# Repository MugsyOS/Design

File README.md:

# Design
All the parts! CAD, PCB and STL files for all of Mugsy's physical components. 

# Mech Control PCB
### Files:
* ****Schematic:**** mech-control-SCH-v0.2.fsch
* ****Board:**** mech-control-BRD-v0.2.fbrd
- - -

# Cone Mech
### Files:
* **Cone Pulley (2 files):** Print main and top.
* **Cone Support (1 file):** Print two for both left and right supports.
* **Stepper Motor Mount (1 file)**: Print one
* **Panels:** 
  * STLs provided for both top and bottom panels.
  * DXF files provided for those with access to a laser or CNC. We use 3mm cast acrylic which works out great. Other material can be used but must be 3mm. 
* **Idler Mount (1 File):** Print two.
- - -
### Additional Parts:
* **Stepper Motor**
  * Model:14HR05-0504S
  * Step Angle: 0.9deg
  * Single Unit Source: [STEPPERONLINE](https://www.omc-stepperonline.com/round-nema-14-bipolar-0-9deg-7ncm-9-91oz-in-0-5a-8-5v-36x12mm-4-wires-14hr05-0504s)
* **Signal** **Breakout PCB**: PCB files will be uploaded shortly. Single PCBs will also be available on the web store end of March 2024. 
* **Ethernet Socket:** RJ45 Connector, PCB Mount
* **M3 Threaded Inserts:**
  * Size: M3*4.6x5.7mm
* **M3 x 8mm Hex Head Machine Screws**
* **2GT Timing Pulley:** 
  * Type: 2M-AF
  * 20 Teeth
  * 6mm bore size
* **GT2 Toothless  Idler Pulleys (2x):** 3mm bore size
- - -
# Spout Mech
### Files:
* ****Spout Pulley Assembly (2 files):**** Print main and cap.
* ****Spout Pulley Assembly (2 files):**** Print main and cap.
* ****Spout Arm(1 file)****: Print one
- - -
### Additional Parts:
* ****Stepper Motor****
  * Model: 17HS08-1004S |
  * Step Angle: 1.8 deg
  * Single Unit Source: [STEPPERONLINE](https://www.omc-stepperonline.com/nema-17-bipolar-1-8deg-16ncm-22-6oz-in-1a-3-7v-42x42x20mm-4-wires-17hs08-1004s)
* ****M8 x 50mm Threaded Rod****
* ****8mm Shaft Lock Collar:**** 
  * 8mm(ID) * 14mm (OD) * 7mm (Depth)
* ****2GT Timing Pulley:****
  * 40 Teeth 
  * 8mm Bore Size
* ****GT2 Belt:**** 
  * 156mm * 6mm
- - -
# Screen Mount/Stabilizer
### Files:
* ****Screen Support:**** Left Side (single)
* ****Screen Support:**** Right Side (double)
* ****Screen Mount Main****: Print one
- - -
****All STEP/Fusion CAD source files will be uploaded as soon as possible.****

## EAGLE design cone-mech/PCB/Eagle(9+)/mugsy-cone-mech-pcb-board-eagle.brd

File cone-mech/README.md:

# Cone Mech
## Files:
* **Cone Pulley (2 files):** Print main and top.
* **Cone Support (1 file):** Print two for both left and right supports.
* **Stepper Motor Mount (1 file)**: Print one
* **Panels:** 
  * STLs provided for both top and bottom panels.
  * DXF files provided for those with access to a laser or CNC. We use 3mm cast acrylic which works out great. Other material can be used but must be 3mm. 
* **Idler Mount (1 File):** Print two.

## Additional Parts:
* **Stepper Motor**
  * Model:14HR05-0504S
  * Step Angle: 0.9deg
  * Single Unit Source: [STEPPERONLINE](https://www.omc-stepperonline.com/round-nema-14-bipolar-0-9deg-7ncm-9-91oz-in-0-5a-8-5v-36x12mm-4-wires-14hr05-0504s)
* **Signal** **Breakout PCB**: PCB files will be uploaded shortly. Single PCBs will also be available on the web store end of March 2024. 
* **Ethernet Socket:** RJ45 Connector, PCB Mount
* **M3 Threaded Inserts:**
  * Size: M3*4.6x5.7mm
* **M3 x 8mm Hex Head Machine Screws**
* **GT2 Timing Pulley:** 
  * Type: 2M-AF
  * 20 Teeth
  * 6mm bore size
* **GT2 Toothless  Idler Pulleys (2x):** 3mm bore size

***All STEP/Fusion CAD source files will be uploaded as soon as possible.***

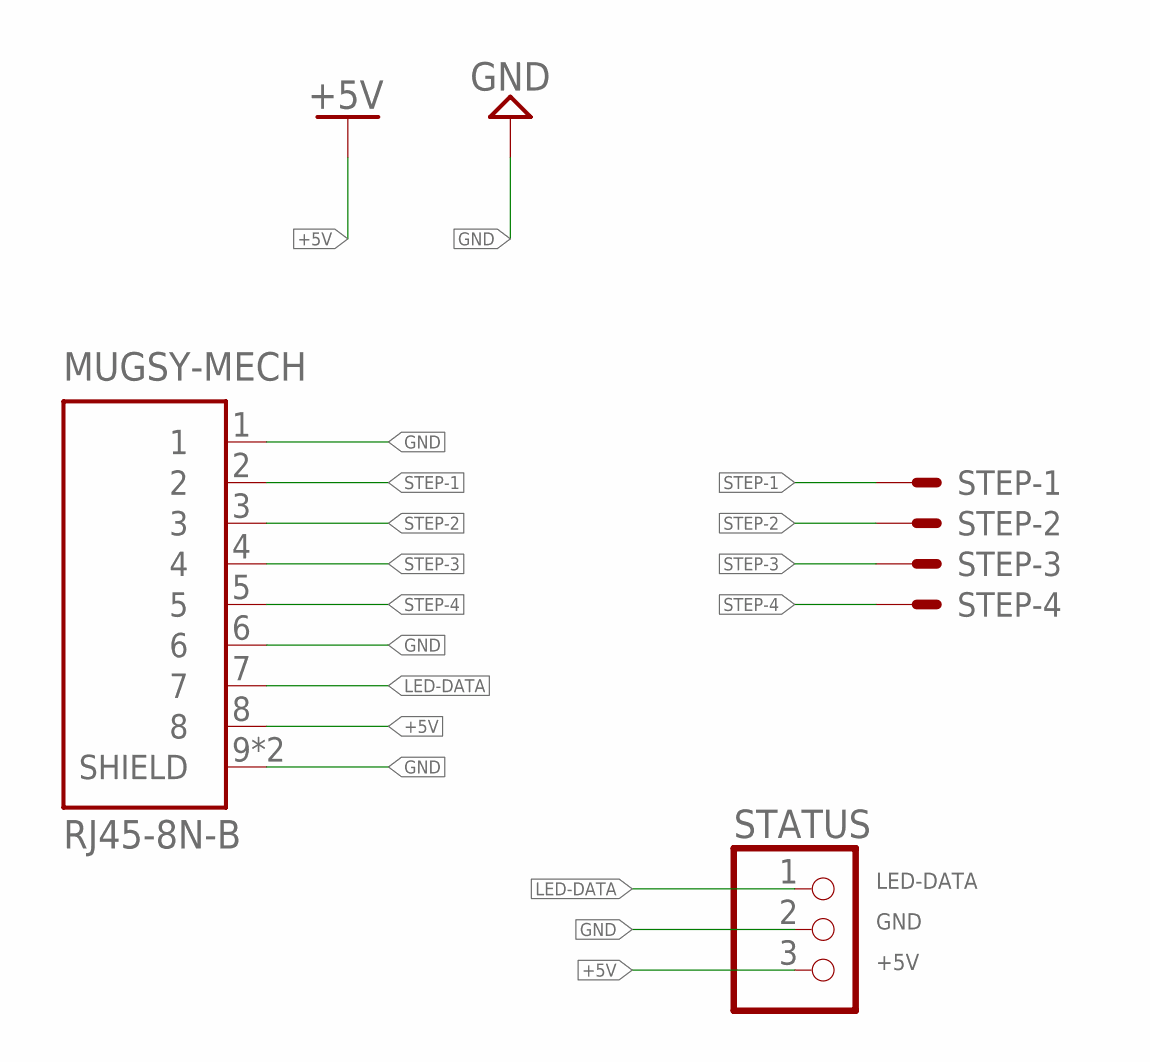
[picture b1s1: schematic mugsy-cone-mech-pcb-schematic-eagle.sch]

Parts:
MUGSY-MECH: RJ45-8N-B; TE_RJ45-8N-B
STATUS: PINHD-1X3CB; 1X03-CLEANBIG
STEP: JST-XH-04-PIN-ROUND-PAD; JST-XH-04-PACKAGE-ROUND-PAD

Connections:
+5V: MUGSY-MECH.8, STATUS.3
GND: MUGSY-MECH.1, MUGSY-MECH.6, MUGSY-MECH.9 (SHIELD), MUGSY-MECH.10 (SHIELD), STATUS.2
LED-DATA: MUGSY-MECH.7, STATUS.1
STEP-1: MUGSY-MECH.2, STEP.1
STEP-2: MUGSY-MECH.3, STEP.2
STEP-3: MUGSY-MECH.4, STEP.3
STEP-4: MUGSY-MECH.5, STEP.4

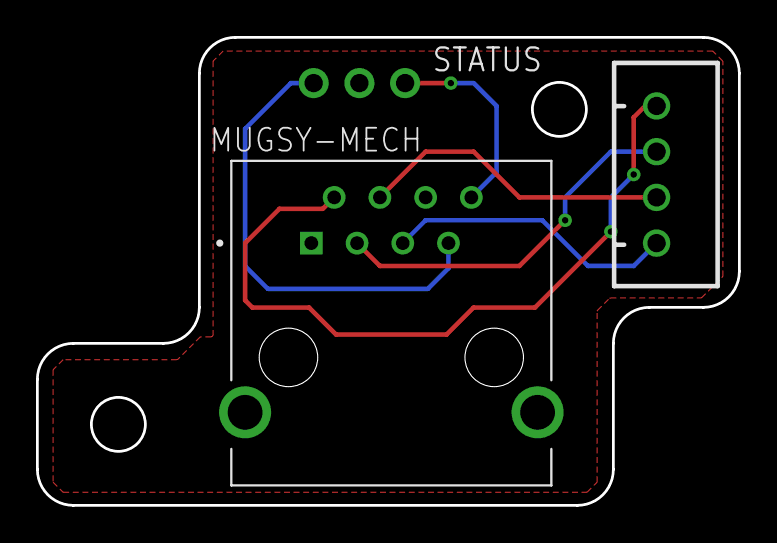
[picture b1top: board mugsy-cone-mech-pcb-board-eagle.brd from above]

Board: 2 copper layers, 39.0 x 26.0 mm, 3 parts (0 on the bottom side), 7 nets.

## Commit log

2024-02-29 add mugsy cone mech PCB board and schematic for fusion and eagle
2024-02-29 add .gitignore
2024-06-03 Add kicad schematic and board for Mech Control PCB
2024-07-22 Add spout limit switch
2025-01-01 add spout-v2 stl files
    With the pump switch, the spout has been redesigned to handle the single tube with larger diameter
2025-02-17 add grinder enclosure design files
2025-08-17 Add files via upload
    Add updated enclosure side cone mech tray mount.
2025-09-07 Add README for outer enclosure panels
2025-10-05 Add limit switch mount for new switch position
2026-01-11 add pi pcb mount
